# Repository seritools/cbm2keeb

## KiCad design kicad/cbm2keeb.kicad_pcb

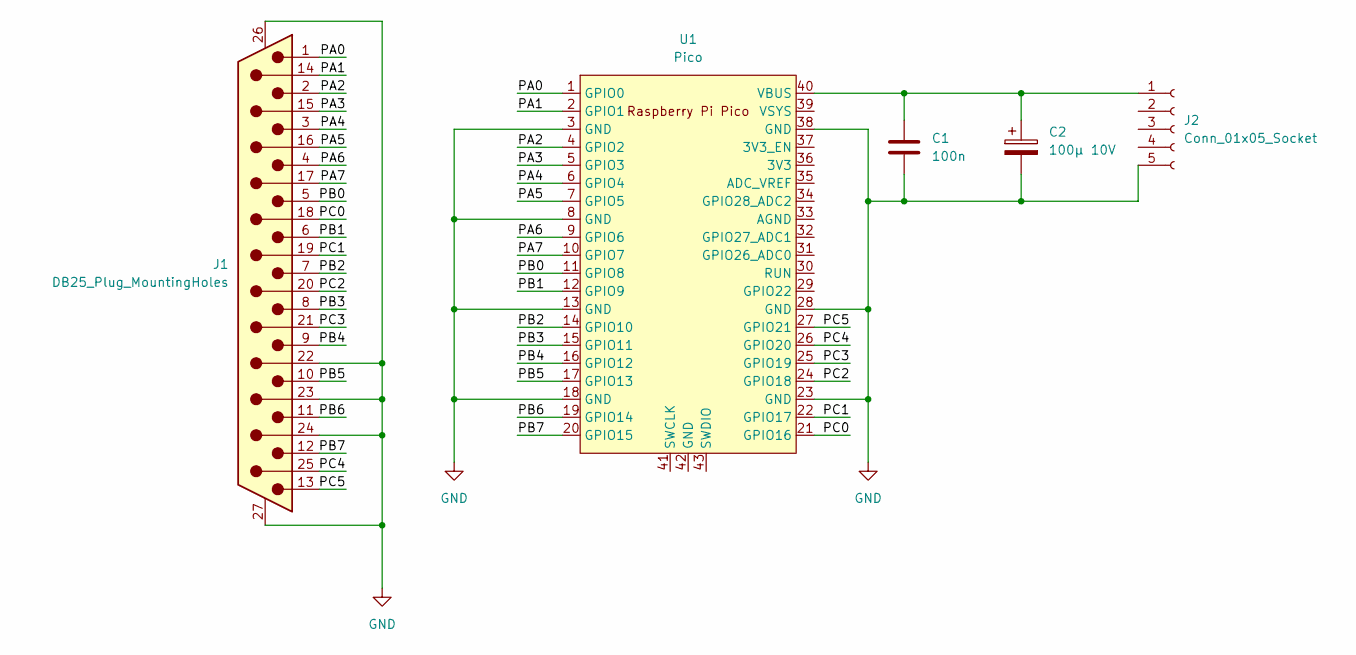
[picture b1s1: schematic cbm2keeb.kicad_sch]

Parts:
C1: 100n; C_0805_2012Metric_Pad1.18x1.45mm_HandSolder
C2: 100µ 10V; CP_Radial_D6.3mm_P2.50mm
J1: DB25_Plug_MountingHoles; DB25-TH_D-SUB-DR-25PCG-BB
J2: Conn_01x05_Socket; PinSocket_1x05_P2.54mm_Vertical
U1: Pico; RPi_Pico_SMD_TH

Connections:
/PA0: J1.1, U1.1 (GPIO0)
/PA1: J1.14, U1.2 (GPIO1)
/PA2: J1.2, U1.4 (GPIO2)
/PA3: J1.15, U1.5 (GPIO3)
/PA4: J1.3, U1.6 (GPIO4)
/PA5: J1.16, U1.7 (GPIO5)
/PA6: J1.4, U1.9 (GPIO6)
/PA7: J1.17, U1.10 (GPIO7)
/PB0: J1.5, U1.11 (GPIO8)
/PB1: J1.6, U1.12 (GPIO9)
/PB2: J1.7, U1.14 (GPIO10)
/PB3: J1.8, U1.15 (GPIO11)
/PB4: J1.9, U1.16 (GPIO12)
/PB5: J1.10, U1.17 (GPIO13)
/PB6: J1.11, U1.19 (GPIO14)
/PB7: J1.12, U1.20 (GPIO15)
/PC0: J1.18, U1.21 (GPIO16)
/PC1: J1.19, U1.22 (GPIO17)
/PC2: J1.20, U1.24 (GPIO18)
/PC3: J1.21, U1.25 (GPIO19)
/PC4: J1.25, U1.26 (GPIO20)
/PC5: J1.13, U1.27 (GPIO21)
GND: C1.2, C2.2, J1.22, J1.23, J1.24, J1.26 (PAD), J1.27 (PAD), J2.5, U1.3 (GND), U1.8 (GND), U1.13 (GND), U1.18 (GND), U1.23 (GND), U1.28 (GND), U1.38 (GND)
unnamed: C1.1, C2.1, J2.1, U1.40 (VBUS)

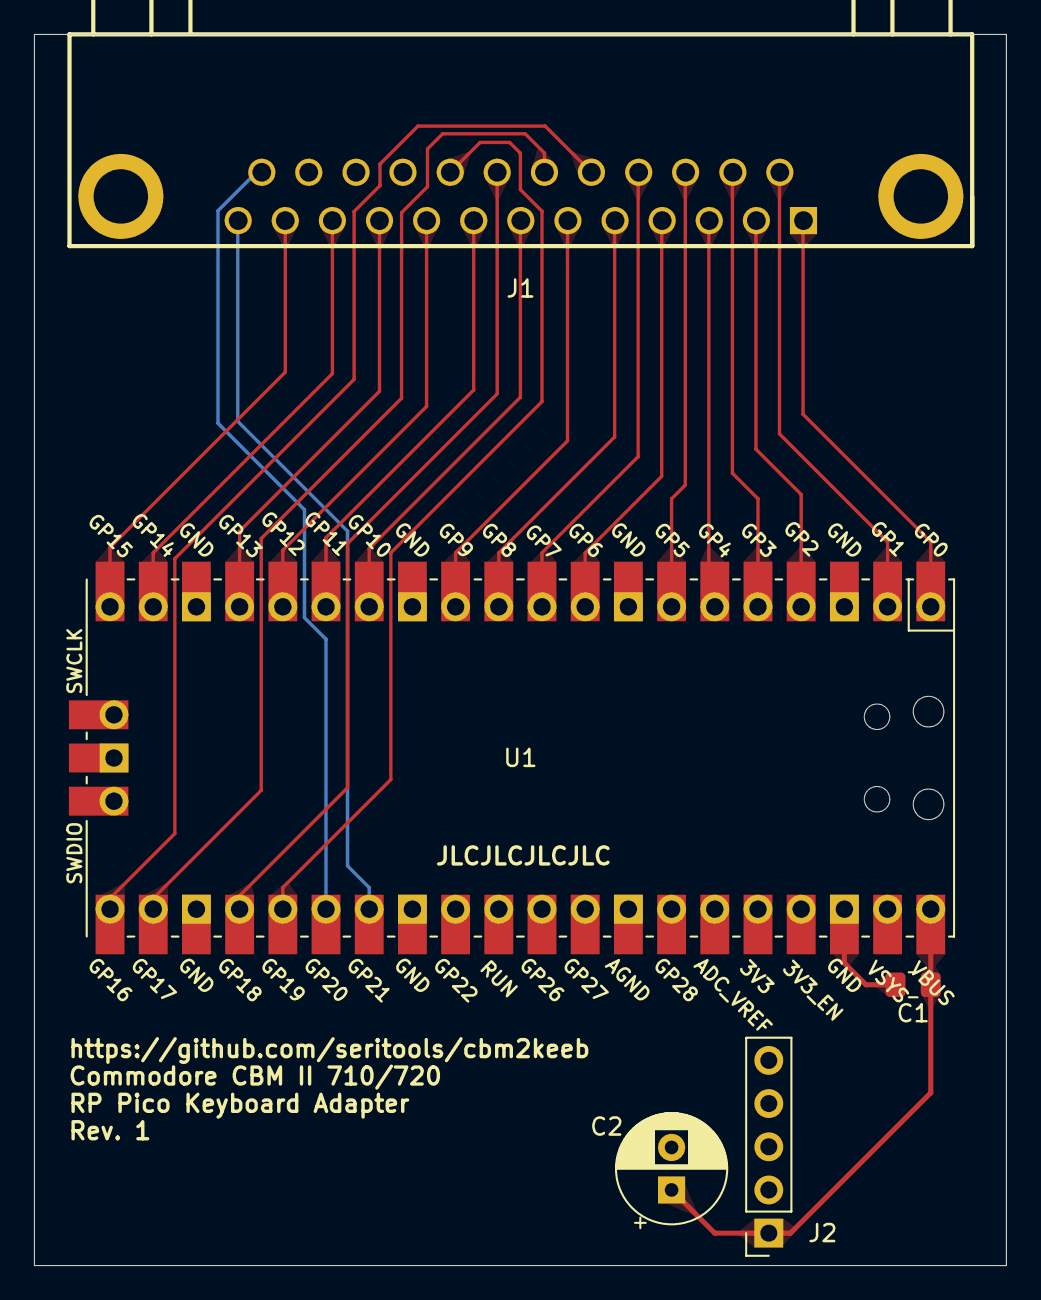
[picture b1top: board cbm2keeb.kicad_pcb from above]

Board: 2 copper layers, 57.1 x 72.4 mm, 5 parts (0 on the bottom side), 24 nets.

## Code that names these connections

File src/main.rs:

#![no_std]
#![no_main]

mod keys;
mod oc;

use defmt as _;
use defmt::{error, info};
use defmt_rtt as _;
use panic_probe as _;
use rtic_monotonics::rp2040_timer_monotonic;

rp2040_timer_monotonic!(Mono);

pub const PINS_IN_MASK: u32 = 0b1111_1111_1111_1111;
pub const PINS_OUT_SHIFT: u8 = 16;

#[rtic::app(
    device = rp_pico::hal::pac, dispatchers = [TIMER_IRQ_1]
)]
mod app {
    use super::*;
    use core::sync::atomic::{AtomicU32, Ordering};
    use hal::gpio::PinState;
    use rp_pico::hal::gpio::PullNone;
    use rp_pico::hal::{self, watchdog::Watchdog};
    use rp_pico::XOSC_CRYSTAL_FREQ;
    use usbh::{
        driver::kbd::{KbdDriver, KbdEvent},
        PollResult, UsbHost,
    };
    use usbh_rp2040::UsbHostBus;

    // Shared resources go here
    #[shared]
    struct Shared {
        col_enabled_pins: [AtomicU32; 4],
    }

    // Local resources go here
    #[local]
    struct Local {
        usb_host: UsbHost<UsbHostBus>,
        kbd_driver: KbdDriver,
        sio: rp_pico::hal::pac::SIO,
    }

    #[init]
    fn init(mut ctx: init::Context) -> (Shared, Local) {
        unsafe { hal::sio::spinlock_reset() };

        // Setup the clock. This is required.
        let mut watchdog = Watchdog::new(ctx.device.WATCHDOG);
        let clocks = oc::init_clocks_and_plls(
            XOSC_CRYSTAL_FREQ,
            ctx.device.XOSC,
            ctx.device.CLOCKS,
            ctx.device.PLL_SYS,
            ctx.device.PLL_USB,
            &mut ctx.device.RESETS,
            &mut watchdog,
        )
        .ok()
        .unwrap();
        Mono::start(ctx.device.TIMER, &ctx.device.RESETS); // default rp2040 clock-rate is 125MHz

        let sio = hal::Sio::new(ctx.device.SIO);

        let pins = hal::gpio::Pins::new(
            ctx.device.IO_BANK0,
            ctx.device.PADS_BANK0,
            sio.gpio_bank0,
            &mut ctx.device.RESETS,
        );

        // config inputs
        pins.gpio0.into_pull_up_input();
        pins.gpio1.into_pull_up_input();
        pins.gpio2.into_pull_up_input();
        pins.gpio3.into_pull_up_input();
        pins.gpio4.into_pull_up_input();
        pins.gpio5.into_pull_up_input();
        pins.gpio6.into_pull_up_input();
        pins.gpio7.into_pull_up_input();
        pins.gpio8.into_pull_up_input();
        pins.gpio9.into_pull_up_input();
        pins.gpio10.into_pull_up_input();
        pins.gpio11.into_pull_up_input();
        pins.gpio12.into_pull_up_input();
        pins.gpio13.into_pull_up_input();
        pins.gpio14.into_pull_up_input();
        pins.gpio15.into_pull_up_input();

        // config outputs. outputs should pull low, or float
        // the CBM II has pull-up resistors on these already
        pins.gpio16
            .into_pull_type::<PullNone>()
            .into_push_pull_output_in_state(PinState::High);
        pins.gpio17
            .into_pull_type::<PullNone>()
            .into_push_pull_output_in_state(PinState::High);
        pins.gpio18
            .into_pull_type::<PullNone>()
            .into_push_pull_output_in_state(PinState::High);
        pins.gpio19
            .into_pull_type::<PullNone>()
            .into_push_pull_output_in_state(PinState::High);
        pins.gpio20
            .into_pull_type::<PullNone>()
            .into_push_pull_output_in_state(PinState::High);
        pins.gpio21
            .into_pull_type::<PullNone>()
            .into_push_pull_output_in_state(PinState::High);

        // config unused gpios
        pins.gpio22.into_pull_down_disabled();
        pins.gpio23.into_pull_down_disabled();
        pins.gpio24.into_pull_down_disabled();
        pins.gpio25.into_pull_down_disabled();
        pins.gpio26.into_pull_down_disabled();
        pins.gpio27.into_pull_down_disabled();
        pins.gpio28.into_pull_down_disabled();
        pins.gpio29.into_pull_down_disabled();

        let usb_host = UsbHost::new(usbh_rp2040::UsbHostBus::new(
            ctx.device.USBCTRL_REGS,
            ctx.device.USBCTRL_DPRAM,
            clocks.usb_clock,
            &mut ctx.device.RESETS,
        ));
        (
            Shared {
                col_enabled_pins: [const { AtomicU32::new(0) }; 4],
            },
            Local {
                usb_host,
                kbd_driver: KbdDriver::new(),
                sio: unsafe { rp_pico::hal::pac::SIO::steal() },
            },
        )
    }

    #[idle(
        local = [sio],
        shared = [&col_enabled_pins]
    )]
    fn idle(ctx: idle::Context) -> ! {
        // 4 bits to 0xFF in those byte positions
        let lookup: [u32; 16] = [
            0x00000000, 0x000000FF, 0x0000FF00, 0x0000FFFF, 0x00FF0000, 0x00FF00FF, 0x00FFFF00,
            0x00FFFFFF, 0xFF000000, 0xFF0000FF, 0xFF00FF00, 0xFF00FFFF, 0xFFFF0000, 0xFFFF00FF,
            0xFFFFFF00, 0xFFFFFFFF,
        ];

        loop {
            // masking not needed, only checking the low bits, as the bit index matches the row
            // index
            let cols_in = !ctx.local.sio.gpio_in().read().bits() as u16; // & PINS_IN_MASK

            let mask = [
                lookup[(cols_in & 0b1111) as usize],
                lookup[((cols_in >> 4) & 0b1111) as usize],
                lookup[((cols_in >> 8) & 0b1111) as usize],
                lookup[((cols_in >> 12) & 0b1111) as usize],
            ];

            let out = (ctx.shared.col_enabled_pins[0].load(Ordering::Relaxed) & mask[0])
                | (ctx.shared.col_enabled_pins[1].load(Ordering::Relaxed) & mask[1])
                | (ctx.shared.col_enabled_pins[2].load(Ordering::Relaxed) & mask[2])
                | (ctx.shared.col_enabled_pins[3].load(Ordering::Relaxed) & mask[3]);
            let [out0, out1, out2, out3] = out.to_ne_bytes();
            let out = !(out0 | out1 | out2 | out3);

            ctx.local
                .sio
                .gpio_out()
                .write(|w| unsafe { w.bits((out as u32) << PINS_OUT_SHIFT) });
        }
    }

    #[task(
        binds = USBCTRL_IRQ,
        local = [usb_host, kbd_driver],
        shared = [&col_enabled_pins]
    )]
    fn usbctrl_irq(ctx: usbctrl_irq::Context) {
        match ctx
            .local
            .usb_host
            .poll(&mut [ctx.local.kbd_driver /* as &mut dyn Driver<_> */])
        {
            PollResult::NoDevice => {
                return;
            }
            PollResult::Busy => {}
            PollResult::Idle => {}
            PollResult::BusError(error) => {
                error!("Bus error: {}", error);
            }
            PollResult::DiscoveryError(dev_addr) => {
                error!("Discovery for device {} failed", dev_addr);
            }
            _ => {}
        }

        match ctx.local.kbd_driver.take_event() {
            None => {}
            Some(event) => match event {
                KbdEvent::DeviceAdded(dev_addr) => {
                    info!("Keyboard with address {} added", dev_addr);
                    ctx.local
                        .kbd_driver
                        .set_idle(dev_addr, 0, ctx.local.usb_host)
                        .ok()
                        .unwrap();
                }
                KbdEvent::DeviceRemoved(dev_addr) => {
                    info!("Keyboard with address {} removed", dev_addr);
                }
                KbdEvent::InputChanged(_, report) => {
                    let mut col_gpio_bits = [0u32; 4];

                    let cast_to_bytes = bytemuck::cast_mut(&mut col_gpio_bits);

                    for key in report.pressed_keys() {
                        key_set(key, cast_to_bytes);
                    }
                    let modifier_status = report.modifier_status;
                    if modifier_status.left_shift() || modifier_status.right_shift() {
                        key_set(keys::KEY_LEFTSHIFT, cast_to_bytes);
                    }
                    if modifier_status.left_ctrl() || modifier_status.right_ctrl() {
                        key_set(keys::KEY_LEFTCTRL, cast_to_bytes);
                    }

                    for (storage, new) in ctx.shared.col_enabled_pins.iter().zip(col_gpio_bits) {
                        storage.store(new, Ordering::Relaxed);
                    }
                }
                _ => {}
            },
        }
    }
}

fn key_set(key: u8, col_gpio_bits: &mut [u8; 16]) {
    unsafe {
        let (col, row_bits) = *keys::INVERSE_KEYMAP.get_unchecked(key as usize);
        *col_gpio_bits.get_unchecked_mut(col as usize) |= row_bits;
    };
}

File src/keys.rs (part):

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
#[rustfmt::skip]
static KEYMAP: [[u8; 16]; 6] = [
    // PB0 ... PB7 → PA0 ... PA7, will be swapped to PA0 ... PA7 → PB0 ... PB7 in the inverse
    // keymap for better alignment when laying traces.

    //                                                                                                                                                            RVS,          GRAPH,
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
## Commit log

2025-01-12 Add kicad project
